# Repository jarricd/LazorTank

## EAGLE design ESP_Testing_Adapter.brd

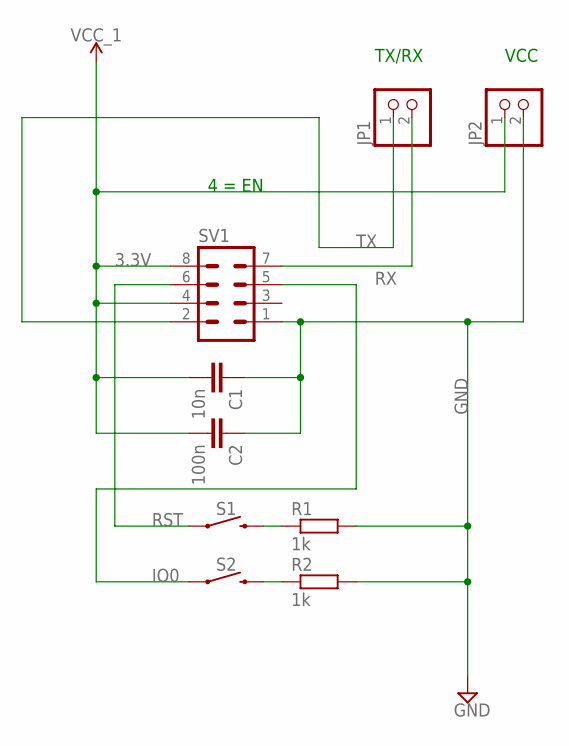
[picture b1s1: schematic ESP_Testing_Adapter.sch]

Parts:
C1: 10n; C2.5-4
C2: 100n; C2.5-4
JP1, JP2: PINHD-1X2; 1X02
R1, R2: 1k; 0207/7
S1, S2: MOMENTARY-SWITCH-SPST-PTH-6.0MM; TACTILE_SWITCH_PTH_6.0MM
SV1: MA04-2

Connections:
3.3V: C1.2, C2.2, JP2.1, SV1.4, SV1.8
GND: C1.1, C2.1, JP2.2, R1.2, R2.2, SV1.1
IO0: S2.1, SV1.5
unnamed: R1.1, S1.3 (2)
unnamed: R2.1, S2.3 (2)
RST: S1.1, SV1.6
RX: JP1.2, SV1.7
TX: JP1.1, SV1.2

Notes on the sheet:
4 = EN
TX/RX
VCC

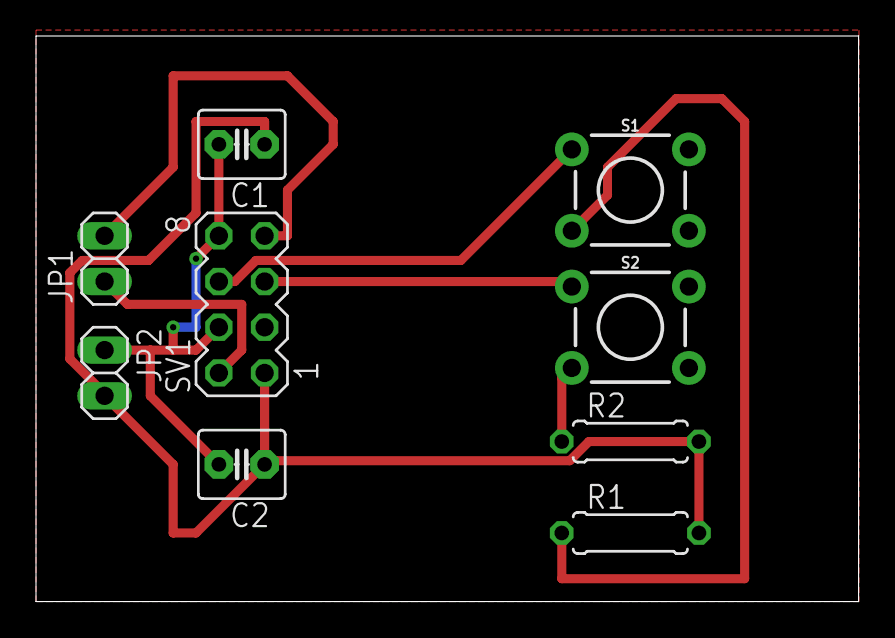
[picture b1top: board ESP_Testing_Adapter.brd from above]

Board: 2 copper layers, 45.7 x 31.4 mm, 9 parts (0 on the bottom side), 8 nets.

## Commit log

2018-04-15 Base board, rev 1. To be tested and manufactured.

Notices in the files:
parts and their libraries:
SparkFun-Switches: Licensing: Creative Commons ShareAlike 4.0 International - https://creativecommons.org/licenses/by-sa/4.0
